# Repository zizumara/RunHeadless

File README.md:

# Description

RunHeadless is a python script that permits application and shutdown control on a
Raspberry Pi via GPIO pins, thus avoiding the need for a keyboard and monitor or
SSH login.  The following features are supported:

1. Launch or terminate an application when a GPIO transitions to low.  If the 
application is not running, launch it.  If the application is already running, 
terminate it.  The GPIO should be connected to ground via a momentary contact 
switch.

2. Shutdown the CPU when a GPIO transitions to low.  The GPIO should be connected to 
ground via a momentary contact switch.

3. Enable/disable application launch and terminate control via a GPIO.  The GPIO 
should be connected to ground via a toggle switch.

4. Enable/disable CPU shutdown control via a GPIO.  The GPIO should be connected to 
ground via a toggle switch.

5. Request graceful application shutdown signaled by the creation of a "flag" file 
recognized by the application.

6. Provide periodic status via GPIO signals (to flash LEDs) for
   a) monitoring service running
   b) application running
   c) system shutdown

# Installation Instructions

These instructions assume that runheadless.py is located in /home/pi/RunHeadless.

1. Copy runheadless.sh to directory /usr/local/bin.

2. Make sure runheadless.sh is executable with

      sudo chmod 755 /usr/local/bin/runheadless.sh

3. Copy runheadless.service to directory /lib/systemd/system.

4. Use the following to enable the service on startup.

      sudo systemctl enable runheadless

5. To check status after startup, use

      sudo systemctl status runheadless

6. To stop the service, use

      sudo systemctl stop runheadless

7. To restart the service, use

      sudo systemctl start runheadless

# Hardware Example

An example control board design is included in KiCAD 6 files.  Refer to the schematic below.
(NOTE: The connector pin numbers below do not represent Raspberry Pi pins.  Refer to runheadless.py to map signal names to Raspberry Pi pins.)

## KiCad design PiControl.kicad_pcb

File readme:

Description

RunHeadless is a python script that permits application and shutdown control on a
Raspberry Pi via GPIO pins, thus avoiding the need for a keyboard and monitor or
SSH login.  The following features are supported:

1. Launch or terminate an application when a GPIO transitions to low.  If the 
application is not running, launch it.  If the application is already running, 
terminate it.  The GPIO should be connected to ground via a momentary contact 
switch.

2. Shutdown the CPU when a GPIO transitions to low.  The GPIO should be connected to 
ground via a momentary contact switch.

3. Enable/disable application launch and terminate control via a GPIO.  The GPIO 
should be connected to ground via a toggle switch.

4. Enable/disable CPU shutdown control via a GPIO.  The GPIO should be connected to 
ground via a toggle switch.

5. Request graceful application shutdown signaled by the creation of a "flag" file 
recognized by the application.

6. Provide periodic status via GPIO signals (to flash LEDs) for
   a) monitoring service running
   b) application running
   c) system shutdown

Installation Instructions

These instructions assume that runheadless.py is located in /home/pi/RunHeadless.

1. Copy runheadless.sh to directory /usr/local/bin.

2. Make sure runheadless.sh is executable with

      sudo chmod 755 /usr/local/bin/runheadless.sh

3. Copy runheadless.service to directory /lib/systemd/system.

4. Use the following to enable the service on startup.

      sudo systemctl enable runheadless

5. To check status after startup, use

      sudo systemctl status runheadless

6. To stop the service, use

      sudo systemctl stop runheadless

7. To restart the service, use

      sudo systemctl start runheadless

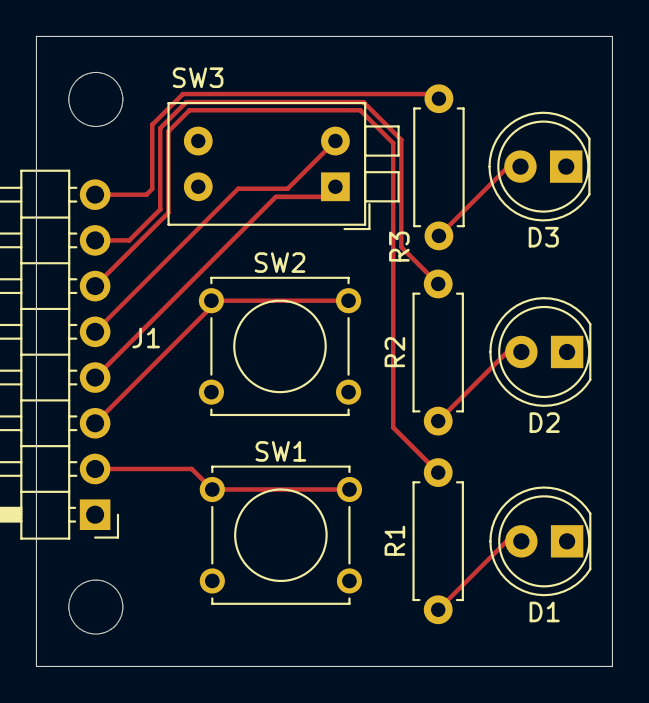
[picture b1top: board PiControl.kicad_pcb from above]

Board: 2 copper layers, 32.0 x 35.0 mm, 10 parts (0 on the bottom side), 11 nets.

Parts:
D1, D2, D3: LED; LED_D5.0mm
J1: PI; PinHeader_1x08_P2.54mm_Horizontal
R1, R2, R3: 330; R_Axial_DIN0207_L6.3mm_D2.5mm_P7.62mm_Horizontal
SW1, SW2: SW_Push_Dual; SW_Tactile_Straight_KSA0Axx1LFTR
SW3: SW_DIP_x02; SW_DIP_SPSTx02_Piano_10.8x6.64mm_W7.62mm_P2.54mm

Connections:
GND: D1.1, D2.1, D3.1, J1.1, SW1.2, SW2.2, SW3.3, SW3.4
unnamed: D1.2, R1.1
unnamed: D2.2, R2.1
unnamed: D3.2, R3.1
unnamed: J1.2, SW1.1
unnamed: J1.3, SW2.1
unnamed: J1.4, SW3.1
unnamed: J1.5, SW3.2
unnamed: J1.6, R1.2
unnamed: J1.7, R2.2
unnamed: J1.8, R3.2

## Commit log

2022-09-26 Add files via upload
    Removed '&' from command which caused script to fail when run as root.
2022-09-26 Add files via upload
    Modified runheadless.py so that if the monitored application terminates, the shutdown status LED is flashed instead of the application running LED. Also added flush of STDOUT so that log file is imme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
